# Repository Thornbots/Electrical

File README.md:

# Electrical Team Repo!

Here is where we store all relevant files for the Electrical team. In here you will store all of the KiCad files that you produce through out the year.

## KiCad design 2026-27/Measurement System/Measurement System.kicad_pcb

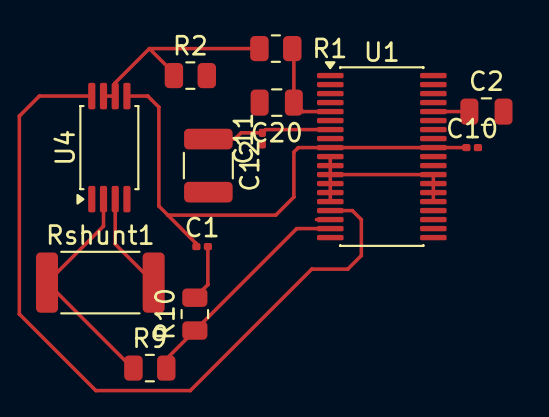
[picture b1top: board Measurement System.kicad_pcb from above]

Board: 2 copper layers, 14 parts (1 on the bottom side), 11 nets.

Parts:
C1: .1uF; C_0201_0603Metric
C2, C20: 10uF; C_0805_2012Metric
C9, C10, C11: 1uF; C_0201_0603Metric
C12: 22uF; C_1210_3225Metric
R1, R10: 10k; R_0805_2012Metric
R2: 16k; R_0805_2012Metric
R9: 90k; R_0805_2012Metric
Rshunt1: 5m; R_2512_6332Metric
U1: ADS8684IDBTR; TSSOP-38_4.4x9.7mm_P0.5mm
U4: INA240A2PWR; TSSOP-8_4.4x3mm_P0.65mm

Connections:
+3V3: C2.1, U1.34 (DVDD)
+5V: C1.1, C9.1, C10.1, U1.9 (AVDD), U1.30 (AVDD__1), U4.5
/PGND: U1.10 (AUX_IN), U1.11 (AUX_GND), U1.12 (NC), U1.13 (NC__1), U1.14 (NC__2), U1.15 (NC__3), U1.24 (NC__4), U1.25 (NC__5), U1.26 (NC__6), U1.27 (NC__7)
/PM01: R9.1, Rshunt1.1, U4.2
/V_DT: Rshunt1.2, U4.3
GND: C1.2, C2.2, C9.2, C10.2, C11.1, C12.2, C20.2, R2.2, R10.2, U1.3 (DAISY), U1.4 (~REFSEL), U1.17 (AIN_0GND), U4.1, U4.4
unnamed: R1.1, R2.1, U4.6, U4.7
unnamed: U1.16 (AIN_0P), U4.8
unnamed: R9.2, R10.1, U1.18 (AIN_1P)
unnamed: C11.2, C12.1, U1.7 (REFCAP)
unnamed: C20.1, R1.2, U1.5 (REFIO)

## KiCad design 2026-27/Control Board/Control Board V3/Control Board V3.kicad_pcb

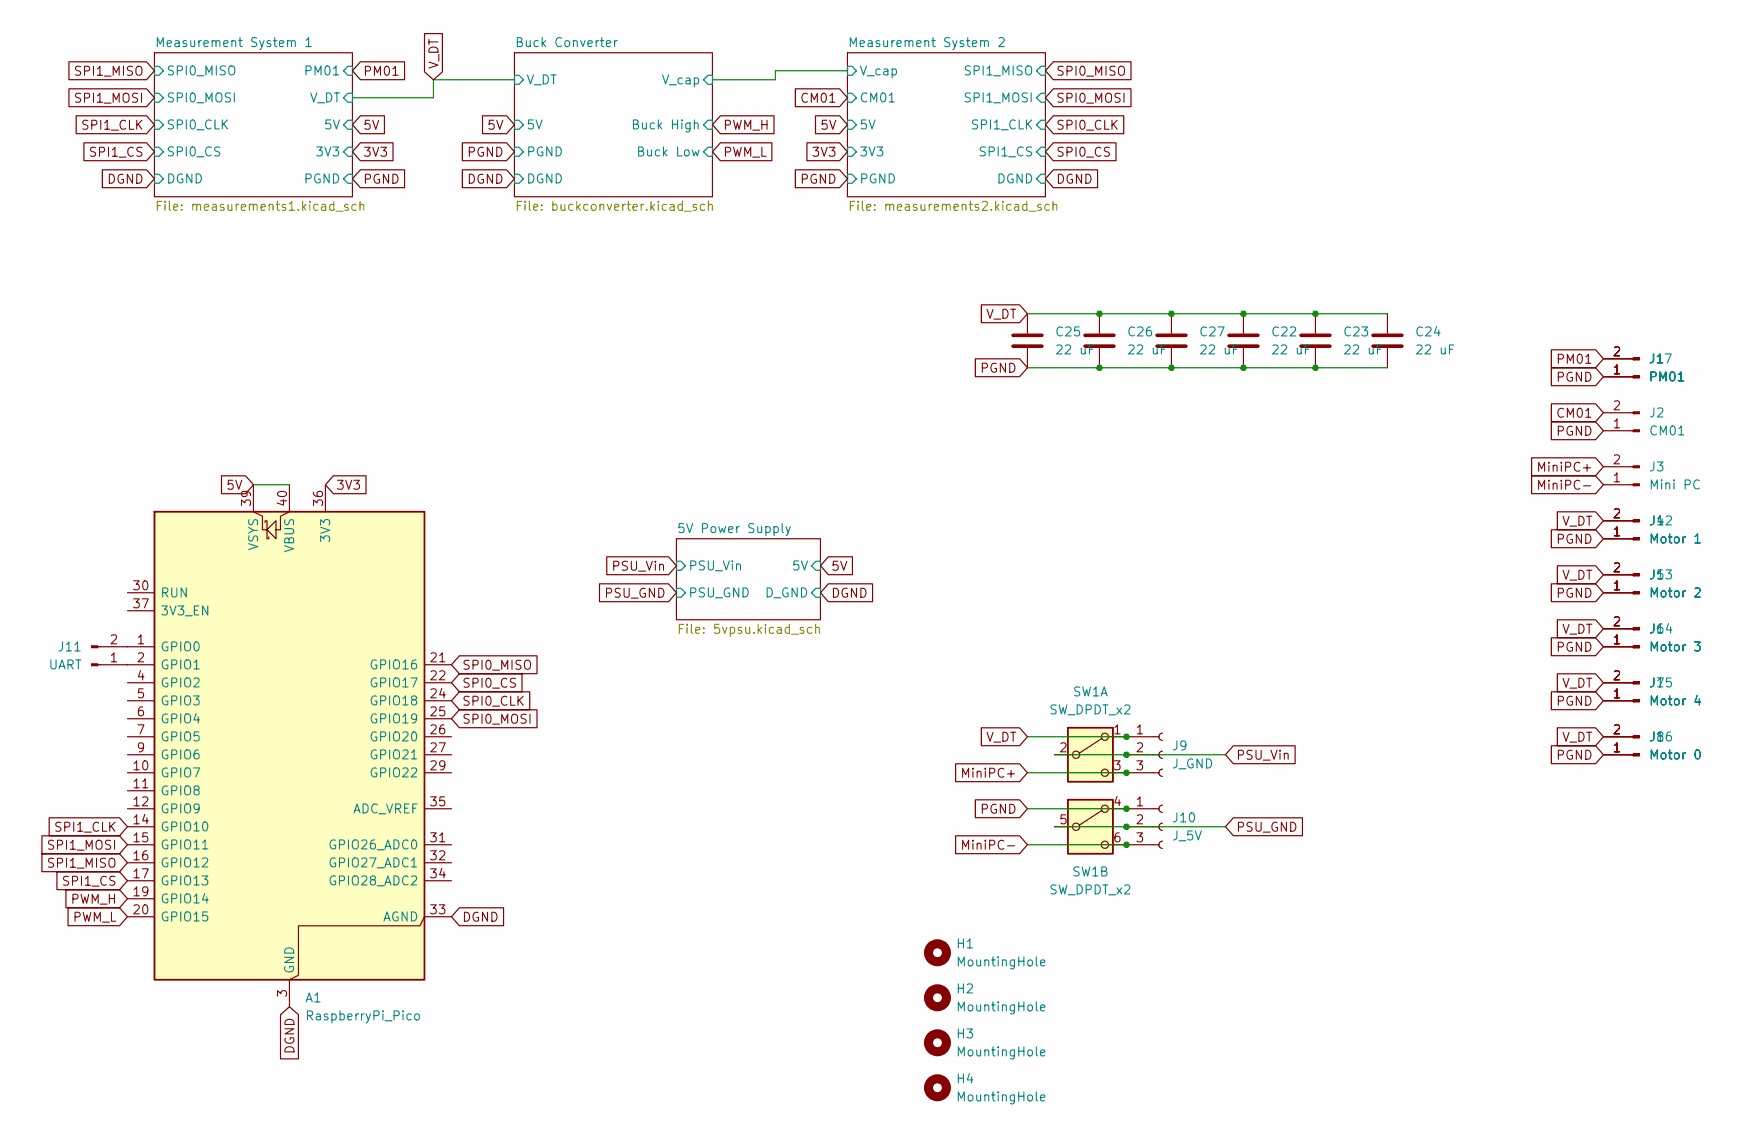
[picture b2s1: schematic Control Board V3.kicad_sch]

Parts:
A1: RaspberryPi_Pico; RaspberryPi_Pico_Common_Unspecified
C22, C23, C24, C25, C26, C27: 22 uF; C_0805_2012Metric
H1, H2, H3, H4: MountingHole; MountingHole_3.2mm_M3
J1: PM01; AMASS_XT30PW-F_1x02_P2.50mm_Horizontal
J2: CM01; AMASS_XT30PW-F_1x02_P2.50mm_Horizontal
J3: Mini PC; AMASS_XT30PW-F_1x02_P2.50mm_Horizontal
J4: Motor 1; AMASS_XT30PW-F_1x02_P2.50mm_Horizontal
J5: Motor 2; AMASS_XT30PW-F_1x02_P2.50mm_Horizontal
J6: Motor 3; AMASS_XT30PW-F_1x02_P2.50mm_Horizontal
J7: Motor 4; AMASS_XT30PW-F_1x02_P2.50mm_Horizontal
J8: Motor 0; AMASS_XT30PW-F_1x02_P2.50mm_Horizontal
J9: J_GND; PinHeader_1x03_P2.54mm_Vertical
J10: J_5V; PinHeader_1x03_P2.54mm_Vertical
J11: UART; PinHeader_1x02_P2.54mm_Vertical
J12: Motor 1; AMASS_XT30PW-M_1x02_P2.50mm_Horizontal
J13: Motor 2; AMASS_XT30PW-M_1x02_P2.50mm_Horizontal
J14: Motor 3; AMASS_XT30PW-M_1x02_P2.50mm_Horizontal
J15: Motor 4; AMASS_XT30PW-M_1x02_P2.50mm_Horizontal
J16: Motor 0; AMASS_XT30PW-M_1x02_P2.50mm_Horizontal
J17: PM01; AMASS_XT30PW-M_1x02_P2.50mm_Horizontal
SW1: SW_DPDT_x2

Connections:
3V3: A1.36 (3V3); also elsewhere on the board
5V: A1.39 (VSYS), A1.40 (VBUS); also elsewhere on the board
CM01: J2.2; also elsewhere on the board
DGND: A1.3 (GND), A1.8 (GND), A1.13 (GND), A1.18 (GND), A1.23 (GND), A1.28 (GND), A1.33 (AGND), A1.38 (GND); also elsewhere on the board
MiniPC+: J3.2, J9.3, SW1.3 (C)
MiniPC-: J3.1, J10.3, SW1.6 (C)
unnamed: A1.1 (GPIO0), J11.2
unnamed: A1.2 (GPIO1), J11.1
PSU_GND: J10.2, SW1.5 (B); also elsewhere on the board
PSU_Vin: J9.2, SW1.2 (B); also elsewhere on the board
PWM_H: A1.19 (GPIO14); also elsewhere on the board
PWM_L: A1.20 (GPIO15); also elsewhere on the board
SPI0_CLK: A1.24 (GPIO18); also elsewhere on the board
SPI0_CS: A1.22 (GPIO17); also elsewhere on the board
SPI0_MISO: A1.21 (GPIO16); also elsewhere on the board
SPI0_MOSI: A1.25 (GPIO19); also elsewhere on the board
SPI1_CLK: A1.14 (GPIO10); also elsewhere on the board
SPI1_CS: A1.17 (GPIO13); also elsewhere on the board
SPI1_MISO: A1.16 (GPIO12); also elsewhere on the board
SPI1_MOSI: A1.15 (GPIO11); also elsewhere on the board
V_DT: C22.1, C23.1, C24.1, C25.1, C26.1, C27.1, J4.2, J5.2, J6.2, J7.2, J8.2, J9.1, J12.2, J13.2, J14.2, J15.2, J16.2, SW1.1 (A); also elsewhere on the board

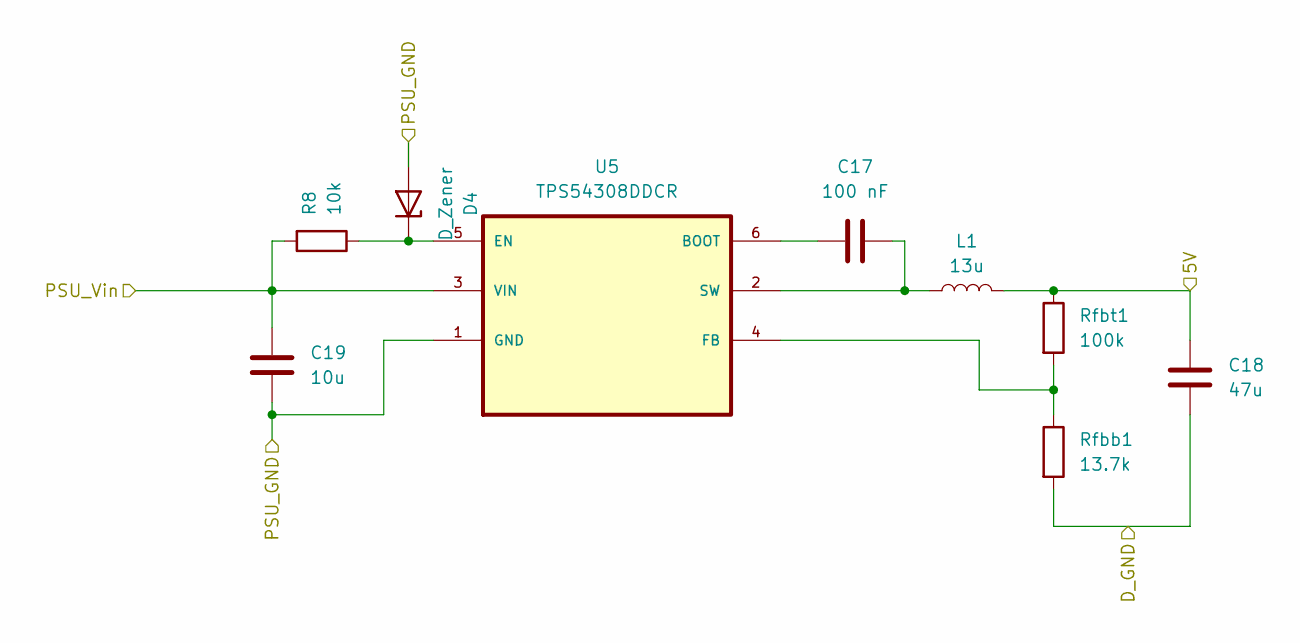
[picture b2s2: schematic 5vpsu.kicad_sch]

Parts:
C17: 100 nF; C_0402_1005Metric
C18: 47u; C_0805_2012Metric
C19: 10u; C_1206_3216Metric
D4: D_Zener; D_SOD-323F
L1: 13u; L_Wuerth_WE-PDF
R8: 10k; R_0603_1608Metric
Rfbb1: 13.7k; R_0402_1005Metric_Pad0.72x0.64mm_HandSolder
Rfbt1: 100k; R_0402_1005Metric_Pad0.72x0.64mm_HandSolder
U5: TPS54308DDCR; SOT-23-6

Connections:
5V: C18.1, L1.2, Rfbt1.1; also elsewhere on the board
DGND: C18.2, Rfbb1.2; also elsewhere on the board
unnamed: D4.1 (K), R8.1, U5.5 (EN)
unnamed: C17.1, U5.6 (BOOT)
unnamed: Rfbb1.1, Rfbt1.2, U5.4 (FB)
unnamed: C17.2, L1.1, U5.2 (SW)
PSU_GND: C19.2, D4.2 (A), U5.1 (GND); also elsewhere on the board
PSU_Vin: C19.1, R8.2, U5.3 (VIN); also elsewhere on the board

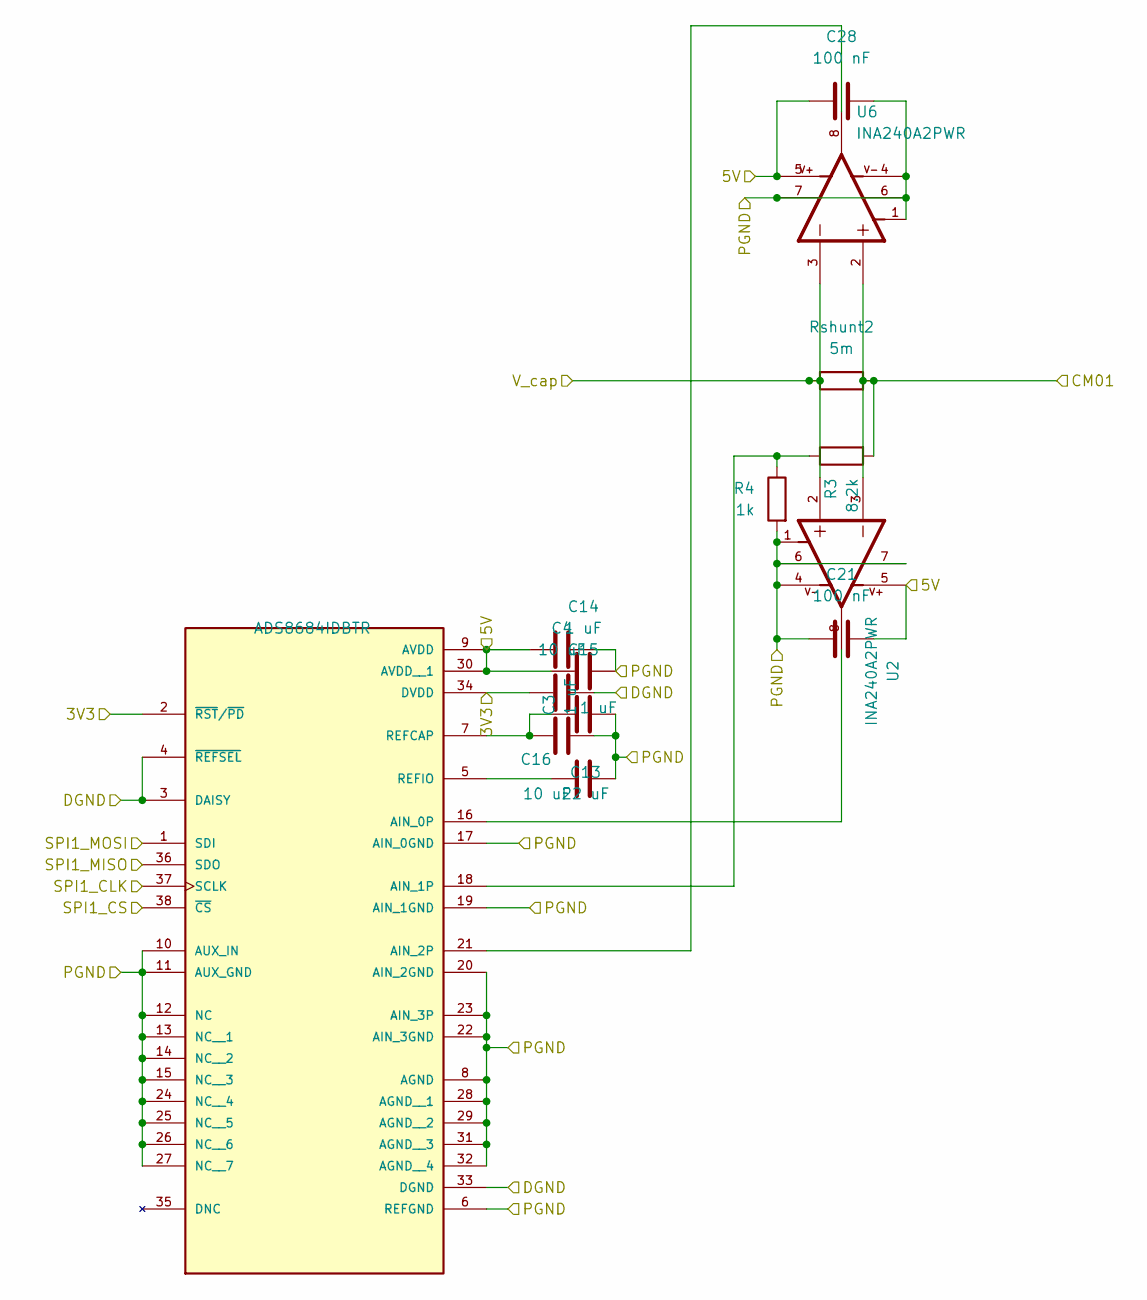
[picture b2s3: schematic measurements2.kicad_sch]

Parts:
C3, C14, C15: 1 uF; C_0603_1608Metric
C4, C16: 10 uF; C_0805_2012Metric
C13: 22 uF; C_1210_3225Metric
C21, C28: 100 nF; C_0402_1005Metric
R3: 8.2k; R_0603_1608Metric
R4: 1k; R_0603_1608Metric
Rshunt2: 5m; R_2512_6332Metric
U1: ADS8684IDBTR; TSSOP-38_4.4x9.7mm_P0.5mm; PARTREV C
U2, U6: INA240A2PWR; TSSOP-8_4.4x3mm_P0.65mm; PARTREV C

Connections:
3V3: C4.1, U1.2 (~RST/~PD), U1.34 (DVDD); also elsewhere on the board
5V: C3.1, C14.1, C21.2, C28.1, U1.9 (AVDD), U1.30 (AVDD__1), U2.5, U6.5; also elsewhere on the board
/Buck Converter/V_cap: Rshunt2.1, U2.2, U6.3; also elsewhere on the board
CM01: R3.2, Rshunt2.2, U2.3, U6.2; also elsewhere on the board
DGND: C4.2, U1.3 (DAISY), U1.4 (~REFSEL), U1.33 (DGND); also elsewhere on the board
unnamed: U1.16 (AIN_0P), U2.8
unnamed: R3.1, R4.1, U1.18 (AIN_1P)
unnamed: U1.21 (AIN_2P), U6.8
unnamed: C13.1, C15.1, U1.7 (REFCAP)
unnamed: C16.1, U1.5 (REFIO)
SPI0_CLK: U1.37 (SCLK); also elsewhere on the board
SPI0_CS: U1.38 (~CS); also elsewhere on the board
SPI0_MISO: U1.36 (SDO); also elsewhere on the board
SPI0_MOSI: U1.1 (SDI); also elsewhere on the board

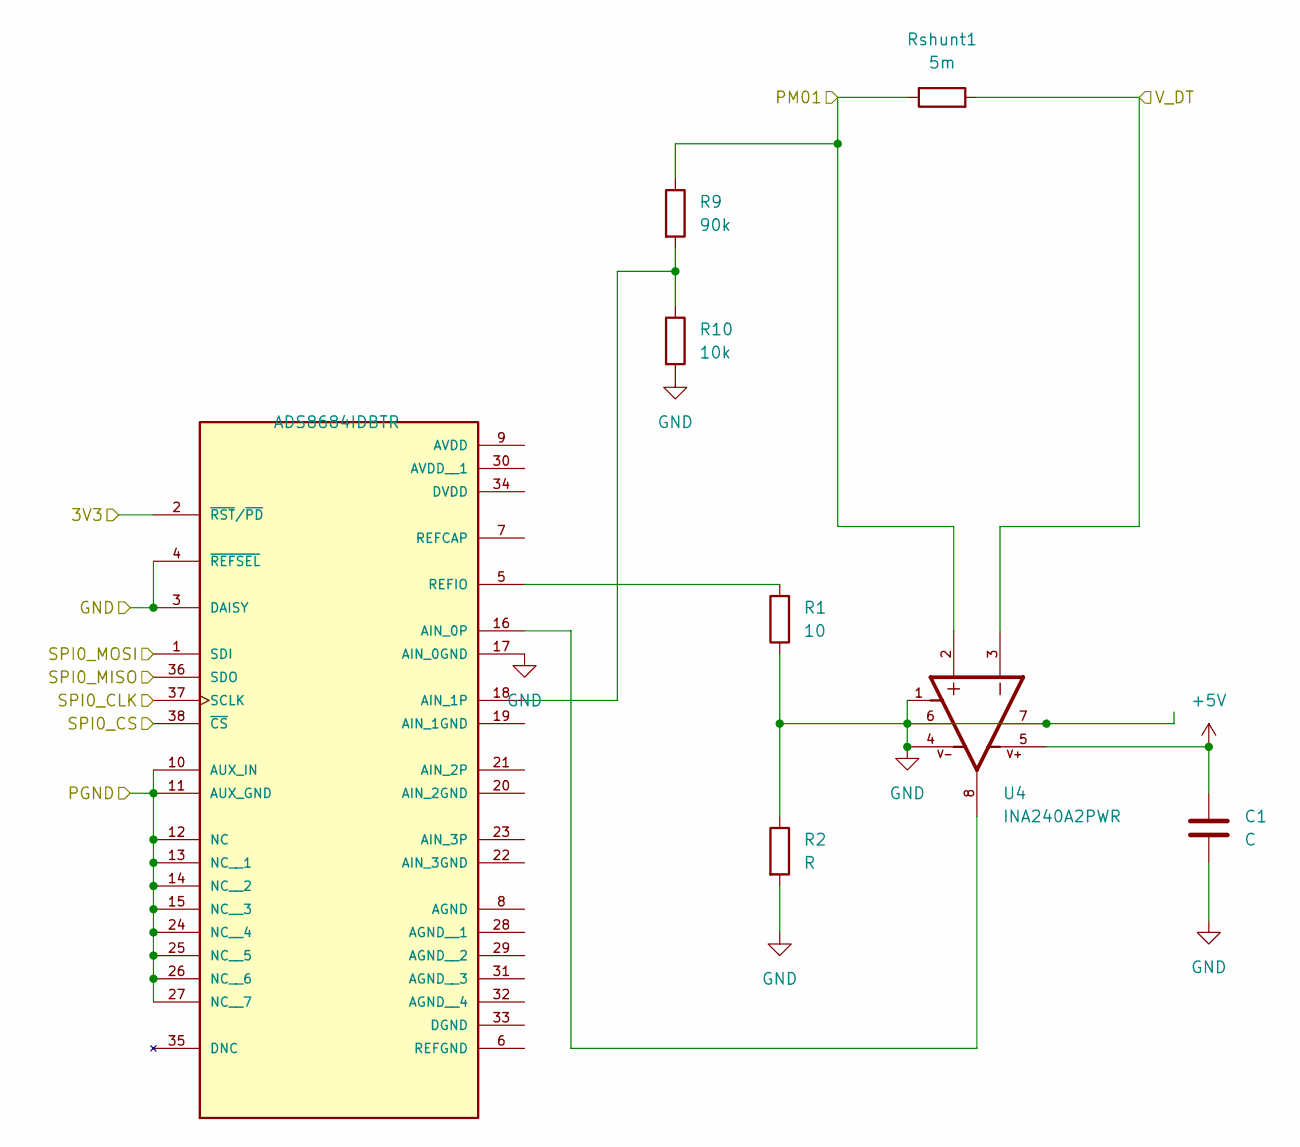
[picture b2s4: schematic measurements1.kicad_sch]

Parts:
C1: C
R1: 10
R2: R
R9: 90k
R10: 10k
Rshunt1: 5m; R_2512_6332Metric
U3: ADS8684IDBTR; TSSOP-38_4.4x9.7mm_P0.5mm; PARTREV C
U4: INA240A2PWR; TSSOP-8_4.4x3mm_P0.65mm; PARTREV C

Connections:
3V3: U3.2 (~RST/~PD), U3.34 (DVDD); also elsewhere on the board
5V: C1.1, U3.9 (AVDD), U3.30 (AVDD__1), U4.5; also elsewhere on the board
DGND: U3.3 (DAISY), U3.4 (~REFSEL), U3.33 (DGND); also elsewhere on the board
unnamed 20: U3.7 (REFCAP); also elsewhere on the board
SPI1_CLK: U3.37 (SCLK); also elsewhere on the board
SPI1_CS: U3.38 (~CS); also elsewhere on the board
SPI1_MISO: U3.36 (SDO); also elsewhere on the board
SPI1_MOSI: U3.1 (SDI); also elsewhere on the board
V_DT: Rshunt1.2, U4.3; also elsewhere on the board

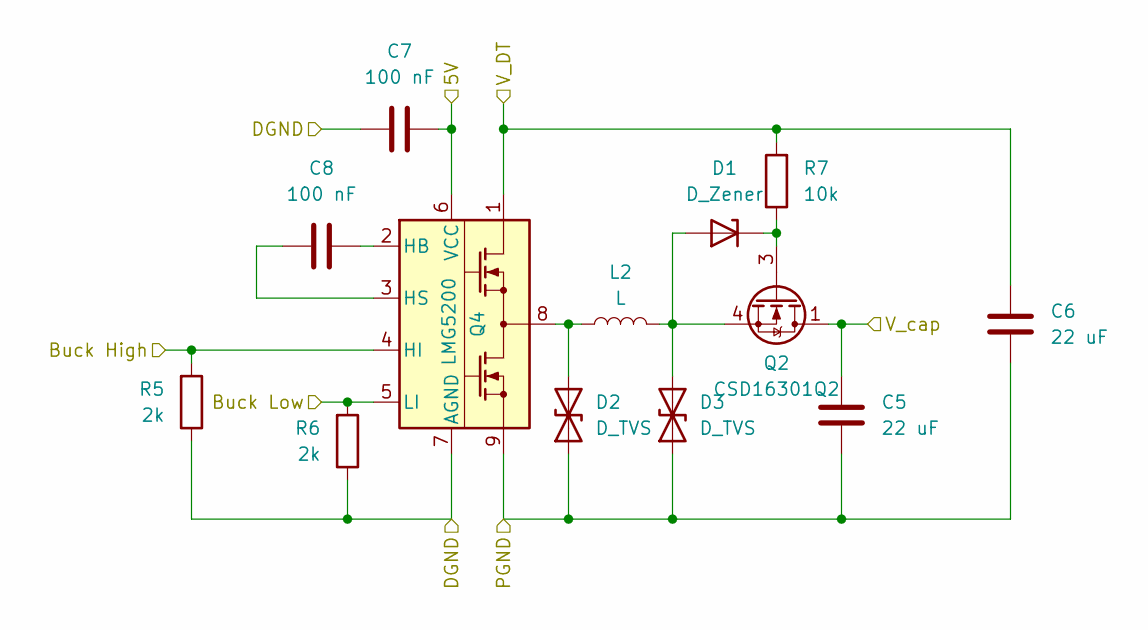
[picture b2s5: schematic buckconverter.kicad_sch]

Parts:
C5, C6: 22 uF; C_0805_2012Metric
C7, C8: 100 nF; C_0402_1005Metric
D1: D_Zener; D_SOD-323F
D2, D3: D_TVS; D_SMB
L2: L; L_Axial_L29.9mm_D14.0mm_P38.00mm_Horizontal_Vishay_IHA-105
Q2: CSD16301Q2; Texas_DQK
Q4: LMG5200; Texas_MOF0009A
R5, R6: 2k; R_0603_1608Metric
R7: 10k; R_0603_1608Metric

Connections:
5V: C7.2, Q4.6 (VCC); also elsewhere on the board
/Buck Converter/V_cap: C5.1, Q2.1 (D), Q2.2 (D), Q2.5 (D), Q2.6 (D), Q2.8 (D); also elsewhere on the board
DGND: C7.1, Q4.7 (AGND), R5.1, R6.1; also elsewhere on the board
unnamed: D1.2 (A), D3.2 (A2), L2.2, Q2.4 (S), Q2.7 (S)
unnamed: D1.1 (K), Q2.3 (G), R7.1
unnamed: D2.2 (A2), L2.1, Q4.8
unnamed: C8.2, Q4.2 (HB)
unnamed: C8.1, Q4.3 (HS)
PWM_H: Q4.4 (HI), R5.2; also elsewhere on the board
PWM_L: Q4.5 (LI), R6.2; also elsewhere on the board
V_DT: C6.1, Q4.1, R7.2; also elsewhere on the board

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
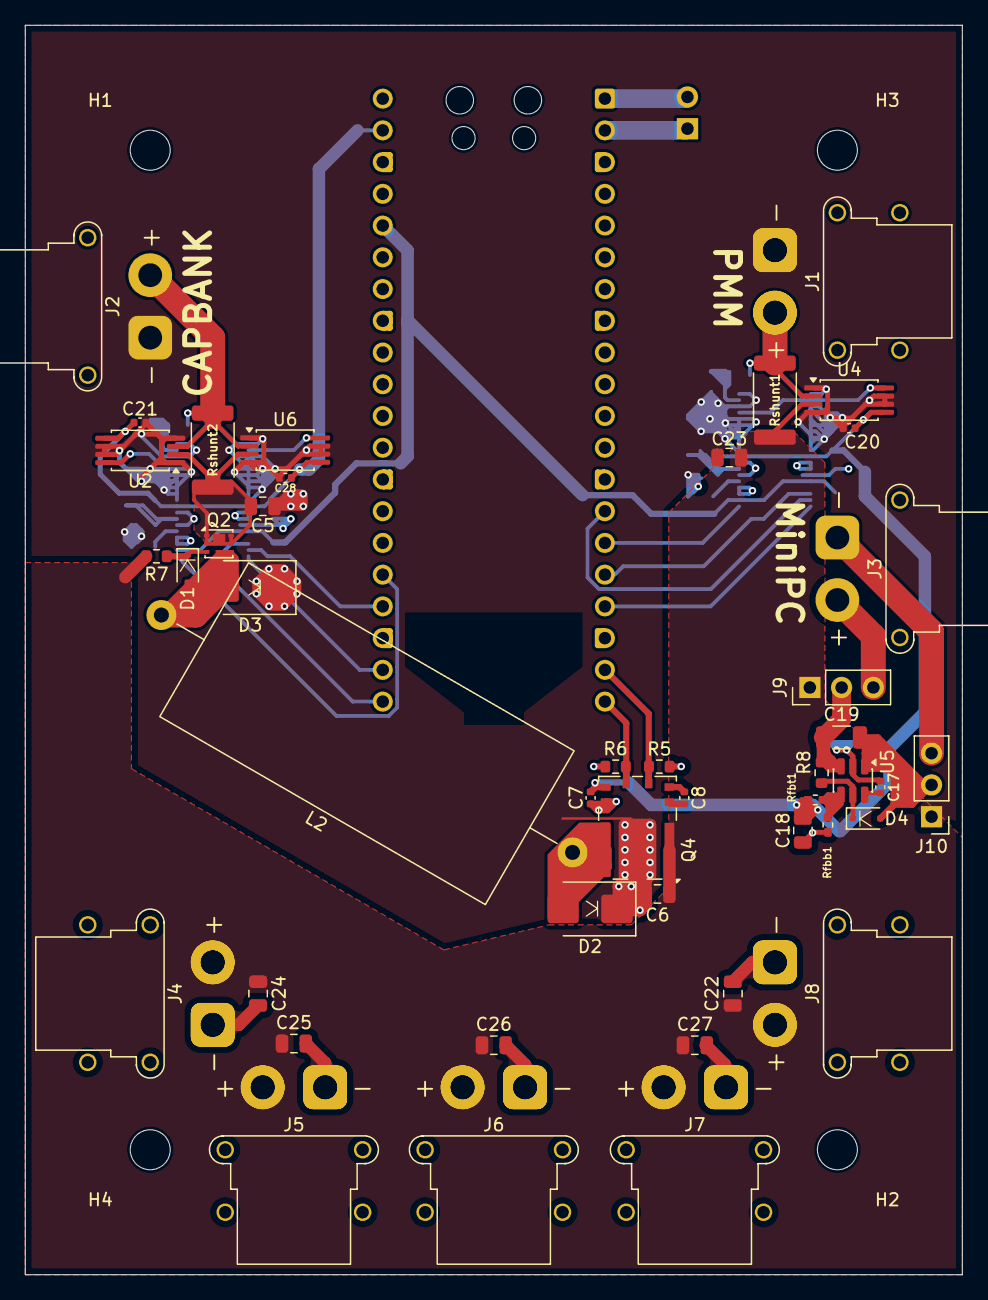
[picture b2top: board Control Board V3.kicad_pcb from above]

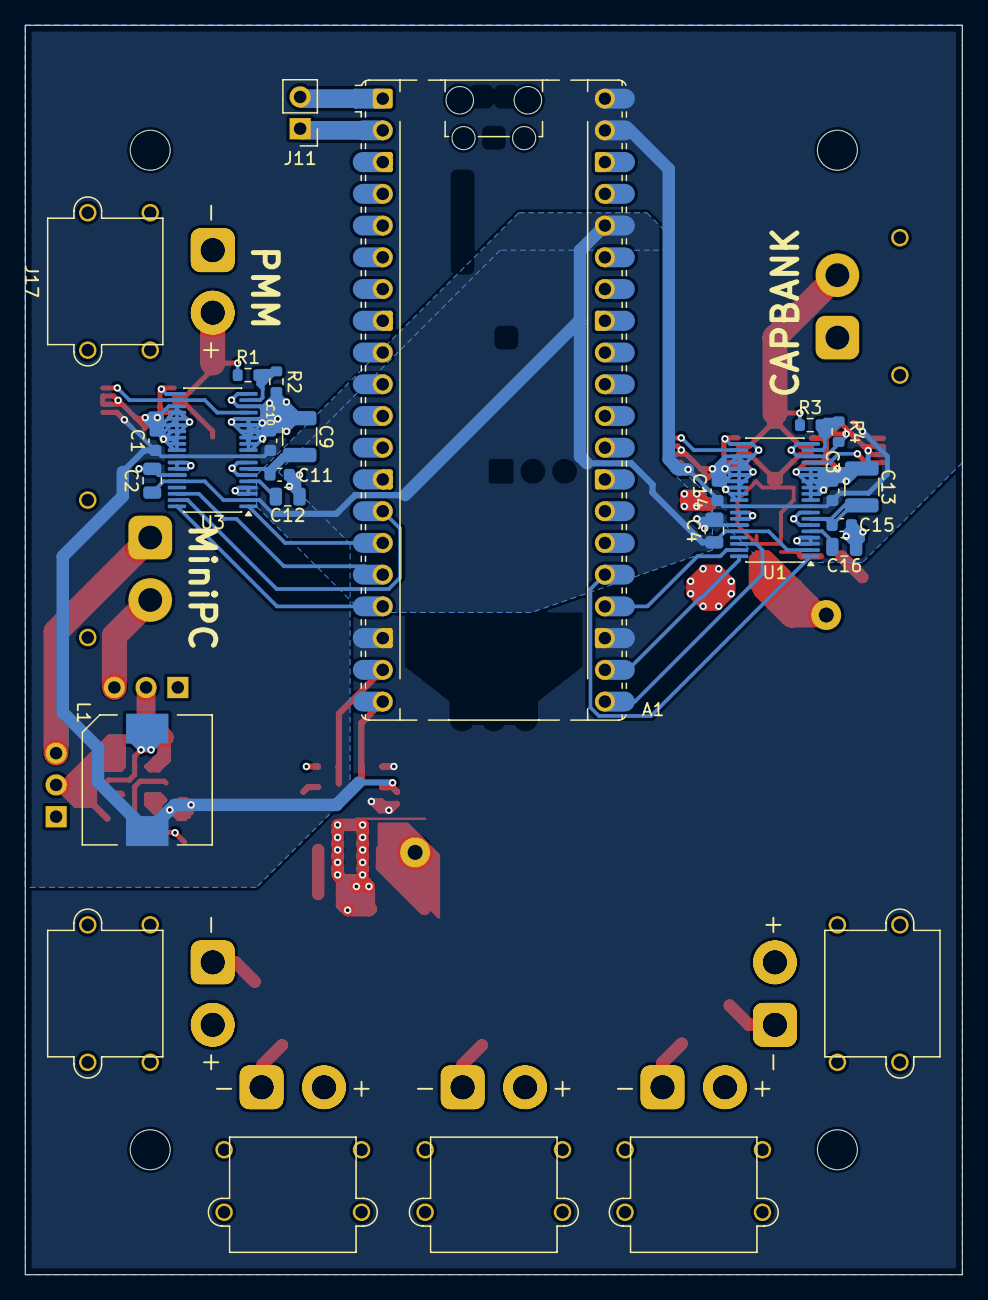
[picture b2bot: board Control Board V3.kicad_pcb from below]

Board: 4 copper layers, 75.0 x 100.0 mm, 76 parts (27 on the bottom side), 42 nets.

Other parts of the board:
C2, C12: 10 uF; C_0805_2012Metric
C9: 22 uF; C_1210_3225Metric
C10, C11: 1 uF; C_0603_1608Metric
C20: 100 nF; C_0402_1005Metric

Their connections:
3V3: C2.1; also elsewhere on the board
5V: C10.1, C20.2; also elsewhere on the board
DGND: C2.2; also elsewhere on the board
unnamed 20: C9.1, C11.1; also elsewhere on the board

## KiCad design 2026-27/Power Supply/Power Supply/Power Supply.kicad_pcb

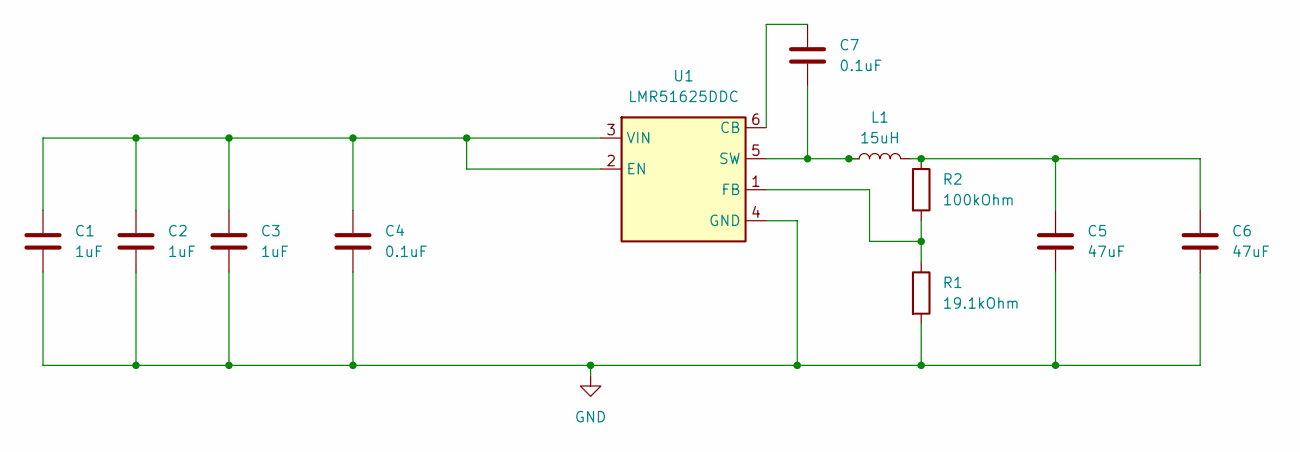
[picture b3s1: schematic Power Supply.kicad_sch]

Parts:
C1, C2, C3: 1uF; C_1206_3216Metric
C4, C7: 0.1uF; C_0603_1608Metric
C5, C6: 47uF; C_1210_3225Metric
L1: 15uH; L_APV_APH1030
R1: 19.1kOhm; R_0805_2012Metric
R2: 100kOhm; R_0603_1608Metric
U1: LMR51625DDC; SOT-23-6

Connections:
GND: C1.2, C2.2, C3.2, C4.2, C5.2, C6.2, R1.2, U1.4 (GND)
unnamed: C5.1, C6.1, L1.2, R2.1
unnamed: C7.1, U1.6 (CB)
unnamed: C1.1, C2.1, C3.1, C4.1, U1.2 (EN), U1.3 (VIN)
unnamed: R1.1, R2.2, U1.1 (FB)
unnamed: C7.2, L1.1, U1.5 (SW)

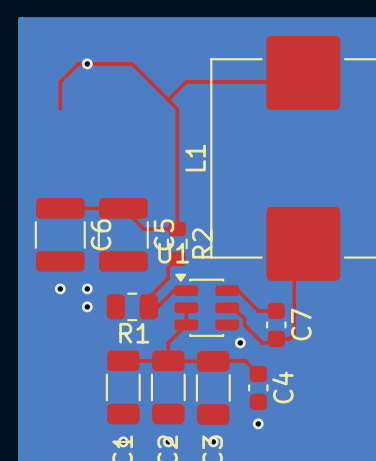
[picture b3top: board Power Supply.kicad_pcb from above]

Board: 2 copper layers, 11 parts (0 on the bottom side), 6 nets.

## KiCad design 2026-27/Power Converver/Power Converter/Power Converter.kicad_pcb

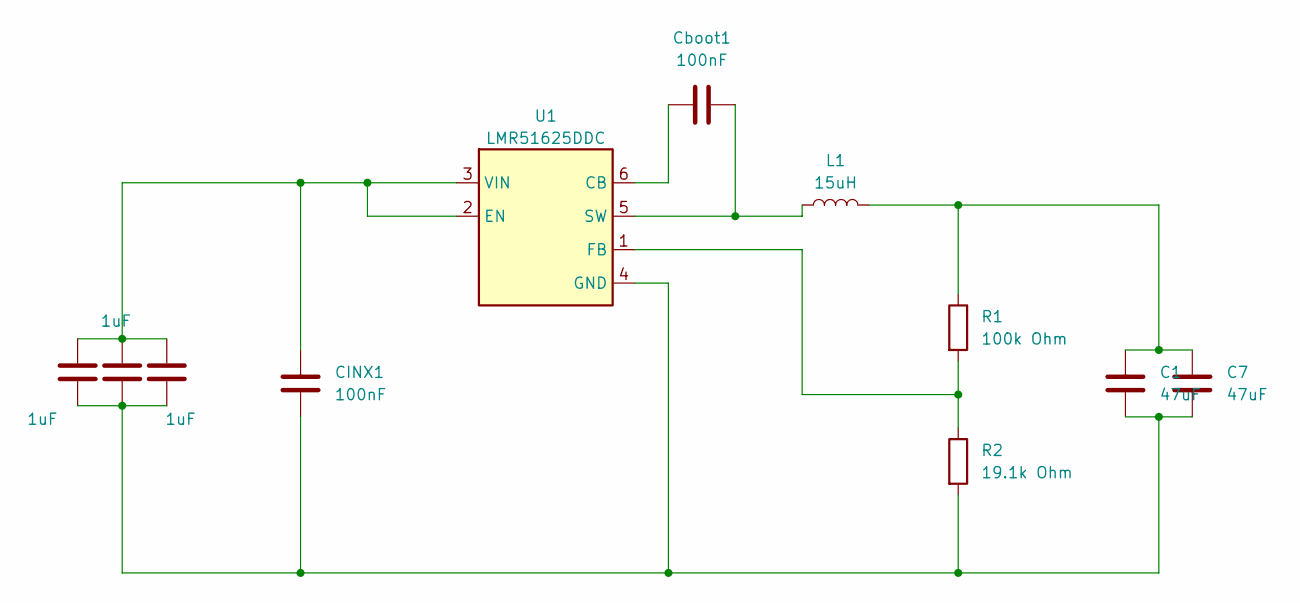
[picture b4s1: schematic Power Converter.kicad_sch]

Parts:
C1, C7: 47uF; C_1210_3225Metric
CIN1, CIN2, CIN3: 1uF; C_1206_3216Metric
CINX1: 100nF; C_0603_1608Metric
Cboot1: 100nF; C_0603_1608Metric
L1: 15uH; L_APV_APH1030
R1: 100k Ohm; R_0805_2012Metric
R2: 19.1k Ohm; R_0603_1608Metric
U1: LMR51625DDC; SOT-23-6

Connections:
unnamed: C1.1, C7.1, L1.2, R1.1
unnamed: Cboot1.2, U1.6 (CB)
unnamed: CIN1.1, CIN2.1, CIN3.1, CINX1.1, U1.2 (EN), U1.3 (VIN)
unnamed: R1.2, R2.1, U1.1 (FB)
unnamed: C1.2, C7.2, CIN1.2, CIN2.2, CIN3.2, CINX1.2, R2.2, U1.4 (GND)
unnamed: Cboot1.1, L1.1, U1.5 (SW)

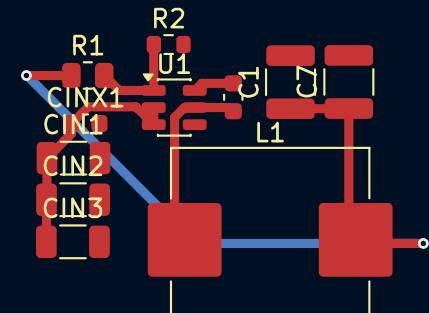
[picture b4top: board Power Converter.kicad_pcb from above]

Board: 2 copper layers, 11 parts (0 on the bottom side), 6 nets.

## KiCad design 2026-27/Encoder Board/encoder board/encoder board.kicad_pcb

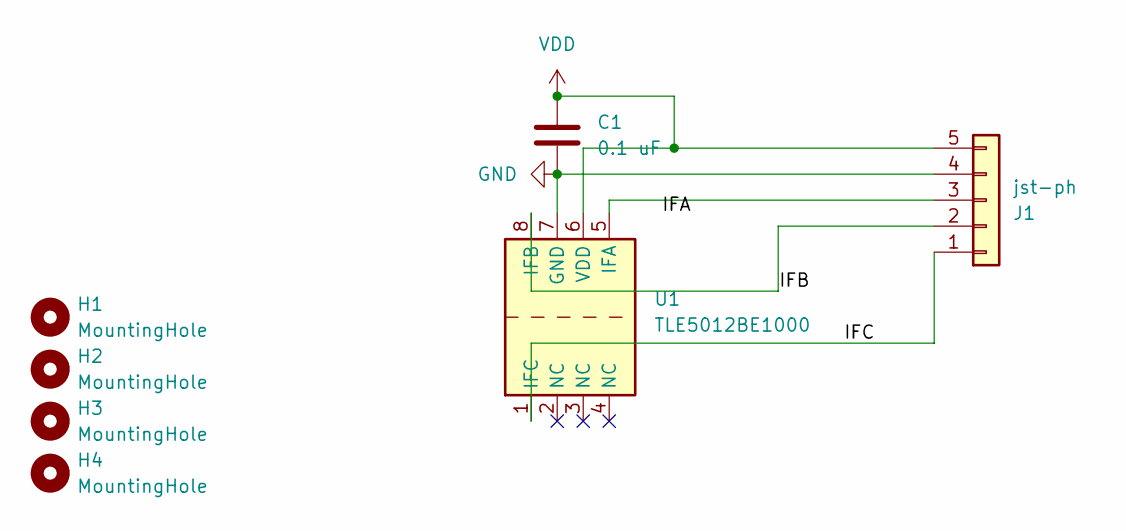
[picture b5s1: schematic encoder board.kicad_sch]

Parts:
C1: 0.1 uF; C_Disc_D9.0mm_W2.5mm_P5.00mm
H1, H2, H3, H4: MountingHole; MountingHole_2.7mm_M2.5
J1: jst-ph; JST_PH_S5B-PH-K_1x05_P2.00mm_Horizontal
U1: TLE5012BE1000; SOIC-8_3.9x4.9mm_P1.27mm

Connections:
/IFA: J1.3, U1.5 (IFA)
/IFC: J1.1, U1.1 (IFC)
GND: C1.2, J1.4, U1.7 (GND)
VDD: C1.1, J1.2, J1.5, U1.6 (VDD), U1.8 (IFB)

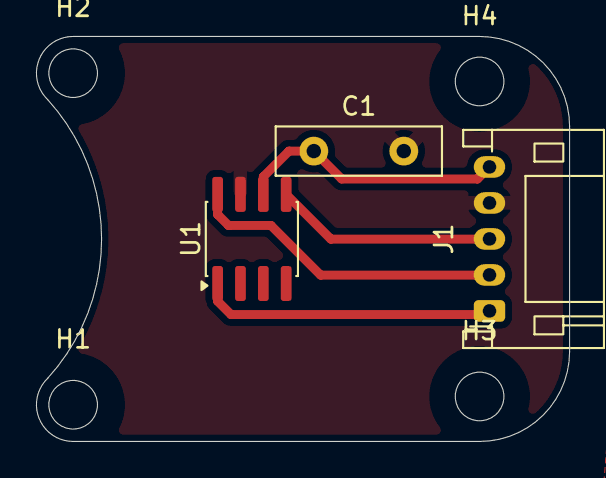
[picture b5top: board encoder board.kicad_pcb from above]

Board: 2 copper layers, 29.6 x 22.5 mm, 7 parts (0 on the bottom side), 4 nets.

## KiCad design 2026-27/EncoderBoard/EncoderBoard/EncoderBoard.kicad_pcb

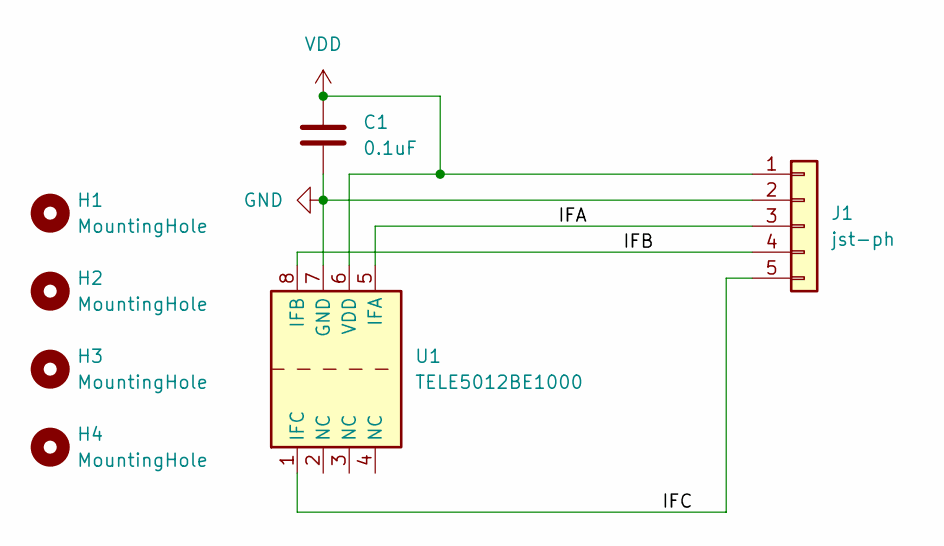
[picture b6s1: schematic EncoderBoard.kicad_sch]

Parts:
C1: 0.1uF; C_Disc_D9.0mm_W2.5mm_P5.00mm
H1, H2, H3, H4: MountingHole; MountingHole_3.2mm_M3
J1: jst-ph; JST_PH_S5B-PH-K_1x05_P2.00mm_Horizontal
U1: TELE5012BE1000; SOIC-8_3.9x4.9mm_P1.27mm

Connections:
/IFA: J1.3, U1.5 (IFA)
/IFB: J1.4, U1.8 (IFB)
/IFC: J1.5, U1.1 (IFC)
GND: C1.2, J1.2, U1.7 (GND)
VDD: C1.1, J1.1, U1.6 (VDD)

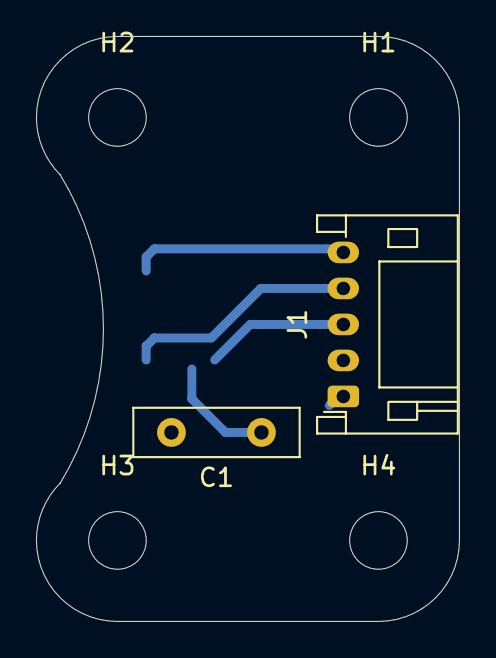
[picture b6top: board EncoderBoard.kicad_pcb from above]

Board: 2 copper layers, 23.5 x 32.5 mm, 7 parts (1 on the bottom side), 5 nets.

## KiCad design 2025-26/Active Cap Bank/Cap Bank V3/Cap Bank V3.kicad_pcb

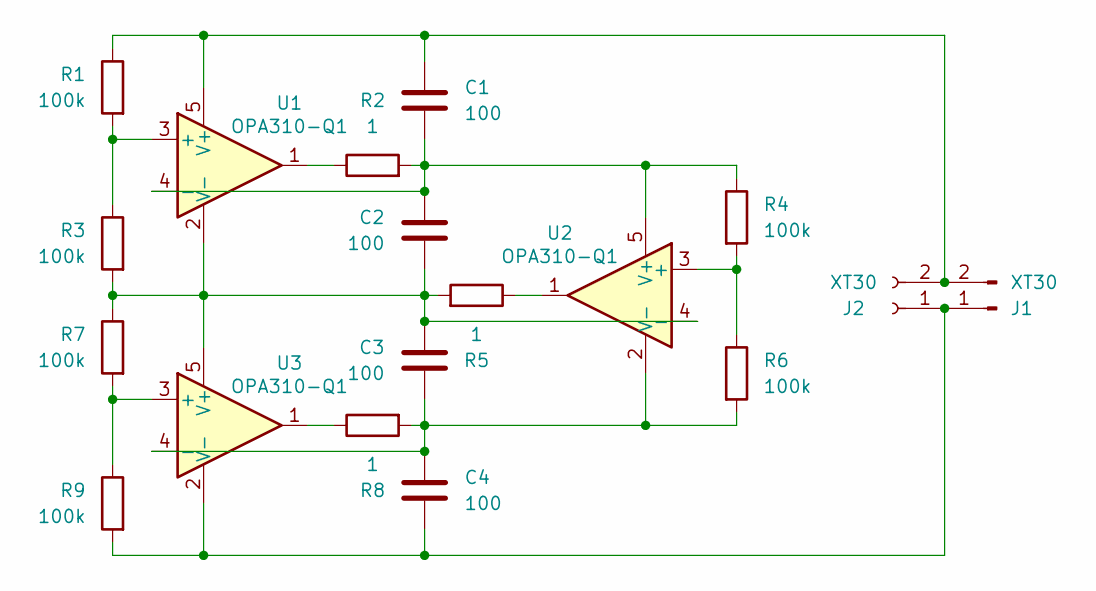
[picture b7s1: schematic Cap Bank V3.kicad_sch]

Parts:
C1, C2, C3, C4: 100; CapTHT
J1: XT30; AMASS_XT30PW-M_1x02_P2.50mm_Horizontal
J2: XT30; AMASS_XT30PW-F_1x02_P2.50mm_Horizontal
R1, R3, R4, R6, R7, R9: 100k; R_0805_2012Metric
R2, R5, R8: 1; R_0805_2012Metric
U1, U2, U3: OPA310-Q1; SOT-23-5

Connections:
unnamed: C4.2, J1.1, J2.1, R9.2, U3.2 (V-)
unnamed: C1.1, J1.2, J2.2, R1.1, U1.5 (V+)
unnamed: R2.1, U1.1
unnamed: R5.1, U2.1
unnamed: R8.1, U3.1
unnamed: R1.2, R3.1, U1.3 (+)
unnamed: C1.2, C2.1, R2.2, R4.1, U1.4 (-), U2.5 (V+)
unnamed: C2.2, C3.1, R3.2, R5.2, R7.1, U1.2 (V-), U2.4 (-), U3.5 (V+)
unnamed: R4.2, R6.1, U2.3 (+)
unnamed: C3.2, C4.1, R6.2, R8.2, U2.2 (V-), U3.4 (-)
unnamed: R7.2, R9.1, U3.3 (+)

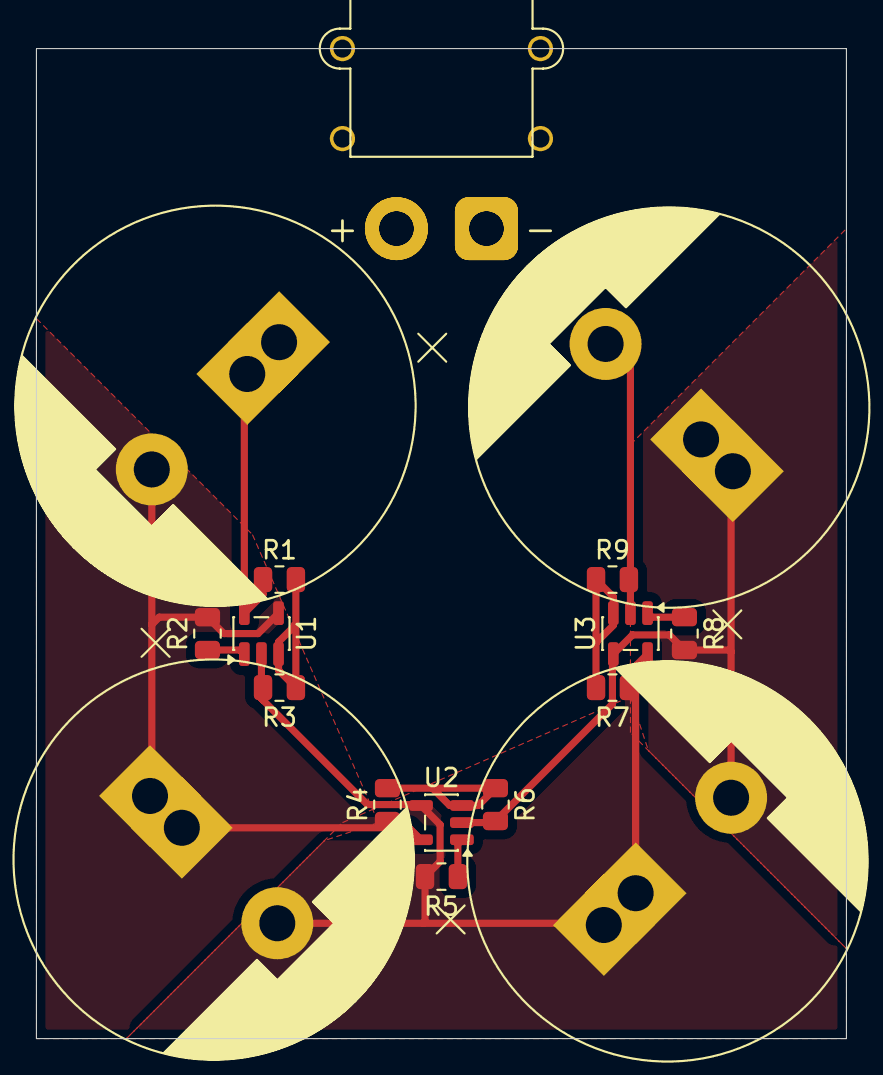
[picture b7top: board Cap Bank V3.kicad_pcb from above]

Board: 2 copper layers, 45.0 x 55.0 mm, 18 parts (1 on the bottom side), 11 nets.
